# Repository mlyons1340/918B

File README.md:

# 918B
A minimal DC/DC boost converter intended for use with guitar pedals.

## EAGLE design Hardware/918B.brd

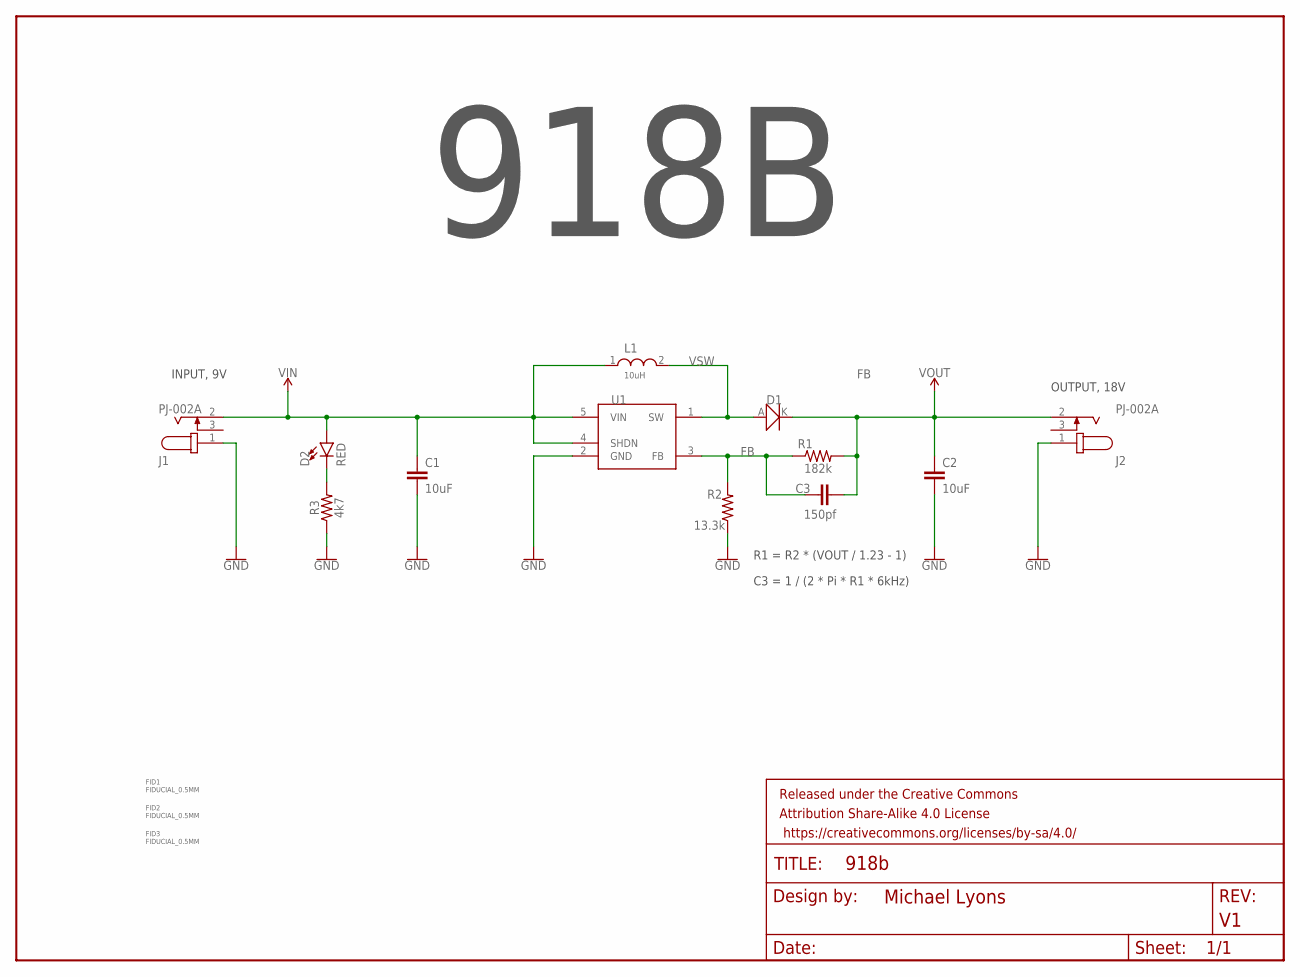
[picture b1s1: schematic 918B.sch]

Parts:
C1, C2: 10uF; 0805; MPN GRM21BR61E106KA73L
C3: 150pf; 0402; MPN C0402C151J5GACTU
D1: PMEG4030EP,115; MPN PMEG4030EP,115
D2: RED; LED-0603; MPN HSMC-C190
FID1, FID2, FID3: FIDUCIAL_0.5MM
FRAME1: FRAME-LETTER; CREATIVE_COMMONS
J1, J2: PJ-002A; CUI_PJ-002A; MPN PJ-002A
L1: 10uH; NR10050T100M; MPN NR10050T100M
R1: 182k; 0402; MPN RC0402FR-07182KL
R2: 13.3k; 0402; MPN RC0402FR-0713K3L
R3: 4k7; 0402; MPN RC0402JR-074K7L
U1: LMR62014XM; SOT-23-5; MPN LMR62014XMFX/NOPB

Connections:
FB: C3.1, R1.1, R2.2, U1.3 (FB)
GND: C1.2, C2.2, J1.1, J2.1, R2.1, R3.1, U1.2 (GND)
NR3: D2.C, R3.2
VIN: C1.1, D2.A, J1.2, L1.1, U1.4 (SHDN), U1.5 (VIN)
VOUT: C2.1, C3.2, D1.K, J2.2, R1.2
VSW: D1.A, L1.2, U1.1 (SW)

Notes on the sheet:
INPUT, 9V
OUTPUT, 18V
R1 = R2 * (VOUT / 1.23 - 1)
C3 = 1 / (2 * Pi * R1 * 6kHz)
918B

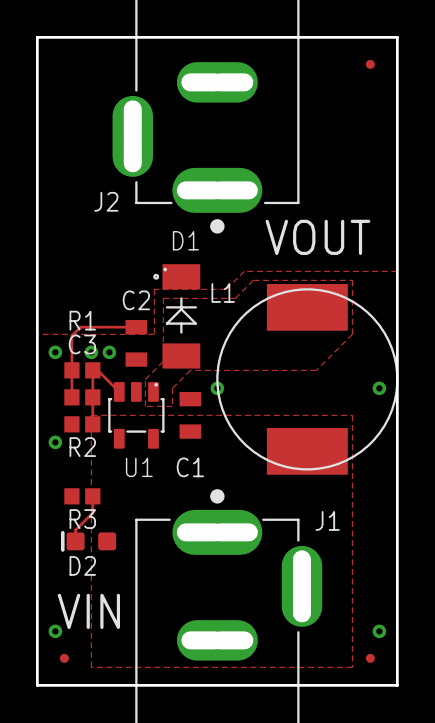
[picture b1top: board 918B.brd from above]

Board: 2 copper layers, 19.2 x 35.2 mm, 17 parts (1 on the bottom side), 6 nets.

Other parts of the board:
U$1: OSHW-LOGO-L

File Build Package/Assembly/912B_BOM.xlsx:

File | 912B_BOM.xlsx
Qty | Designator | MPN | Value | Package | DNP
1 | U1 | LMR62014XMFX/NOPB | LMR62014XM | SOT-23-5
1 | D1 | PMEG4030EP | PMEG4030EP,115 | PMEG4030EP,115
2 | C1, C2 | GRM21BR61E106KA73L | 10uF | 0805
1 | L1 | NR10050T100M | 10uH | NR10050T100M
1 | R2 | RC0402FR-0713K3L | 13.3k | 0402
1 | C3 | CC0402JRNPO9BN221 | 220pf | 0402
1 | R1 | RC0402FR-07118KL | 118k | 0402
1 | R3 | RC0402JR-074K7L | 4k7 | 0402
2 | J1, J2 | PJ-002A | PJ-002A | CUI_PJ-002A
1 | D2 | HSMC-C190 | RED | LED-0603

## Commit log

2020-04-28 V1 release
    V1 release.
2020-05-05 fixed BOM
2020-05-05 moved files to top level folder.

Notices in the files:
parts and their libraries:
SparkFun-Capacitors: Licensing: Creative Commons ShareAlike 4.0 International - https://creativecommons.org/licenses/by-sa/4.0
SparkFun-Aesthetics: Released under the Creative Commons Attribution Share-Alike 4.0 License
SparkFun-Aesthetics: https://creativecommons.org/licenses/by-sa/4.0
